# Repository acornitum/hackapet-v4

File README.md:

# hackapet pcb, v4

this is a wip!! it is not done yet

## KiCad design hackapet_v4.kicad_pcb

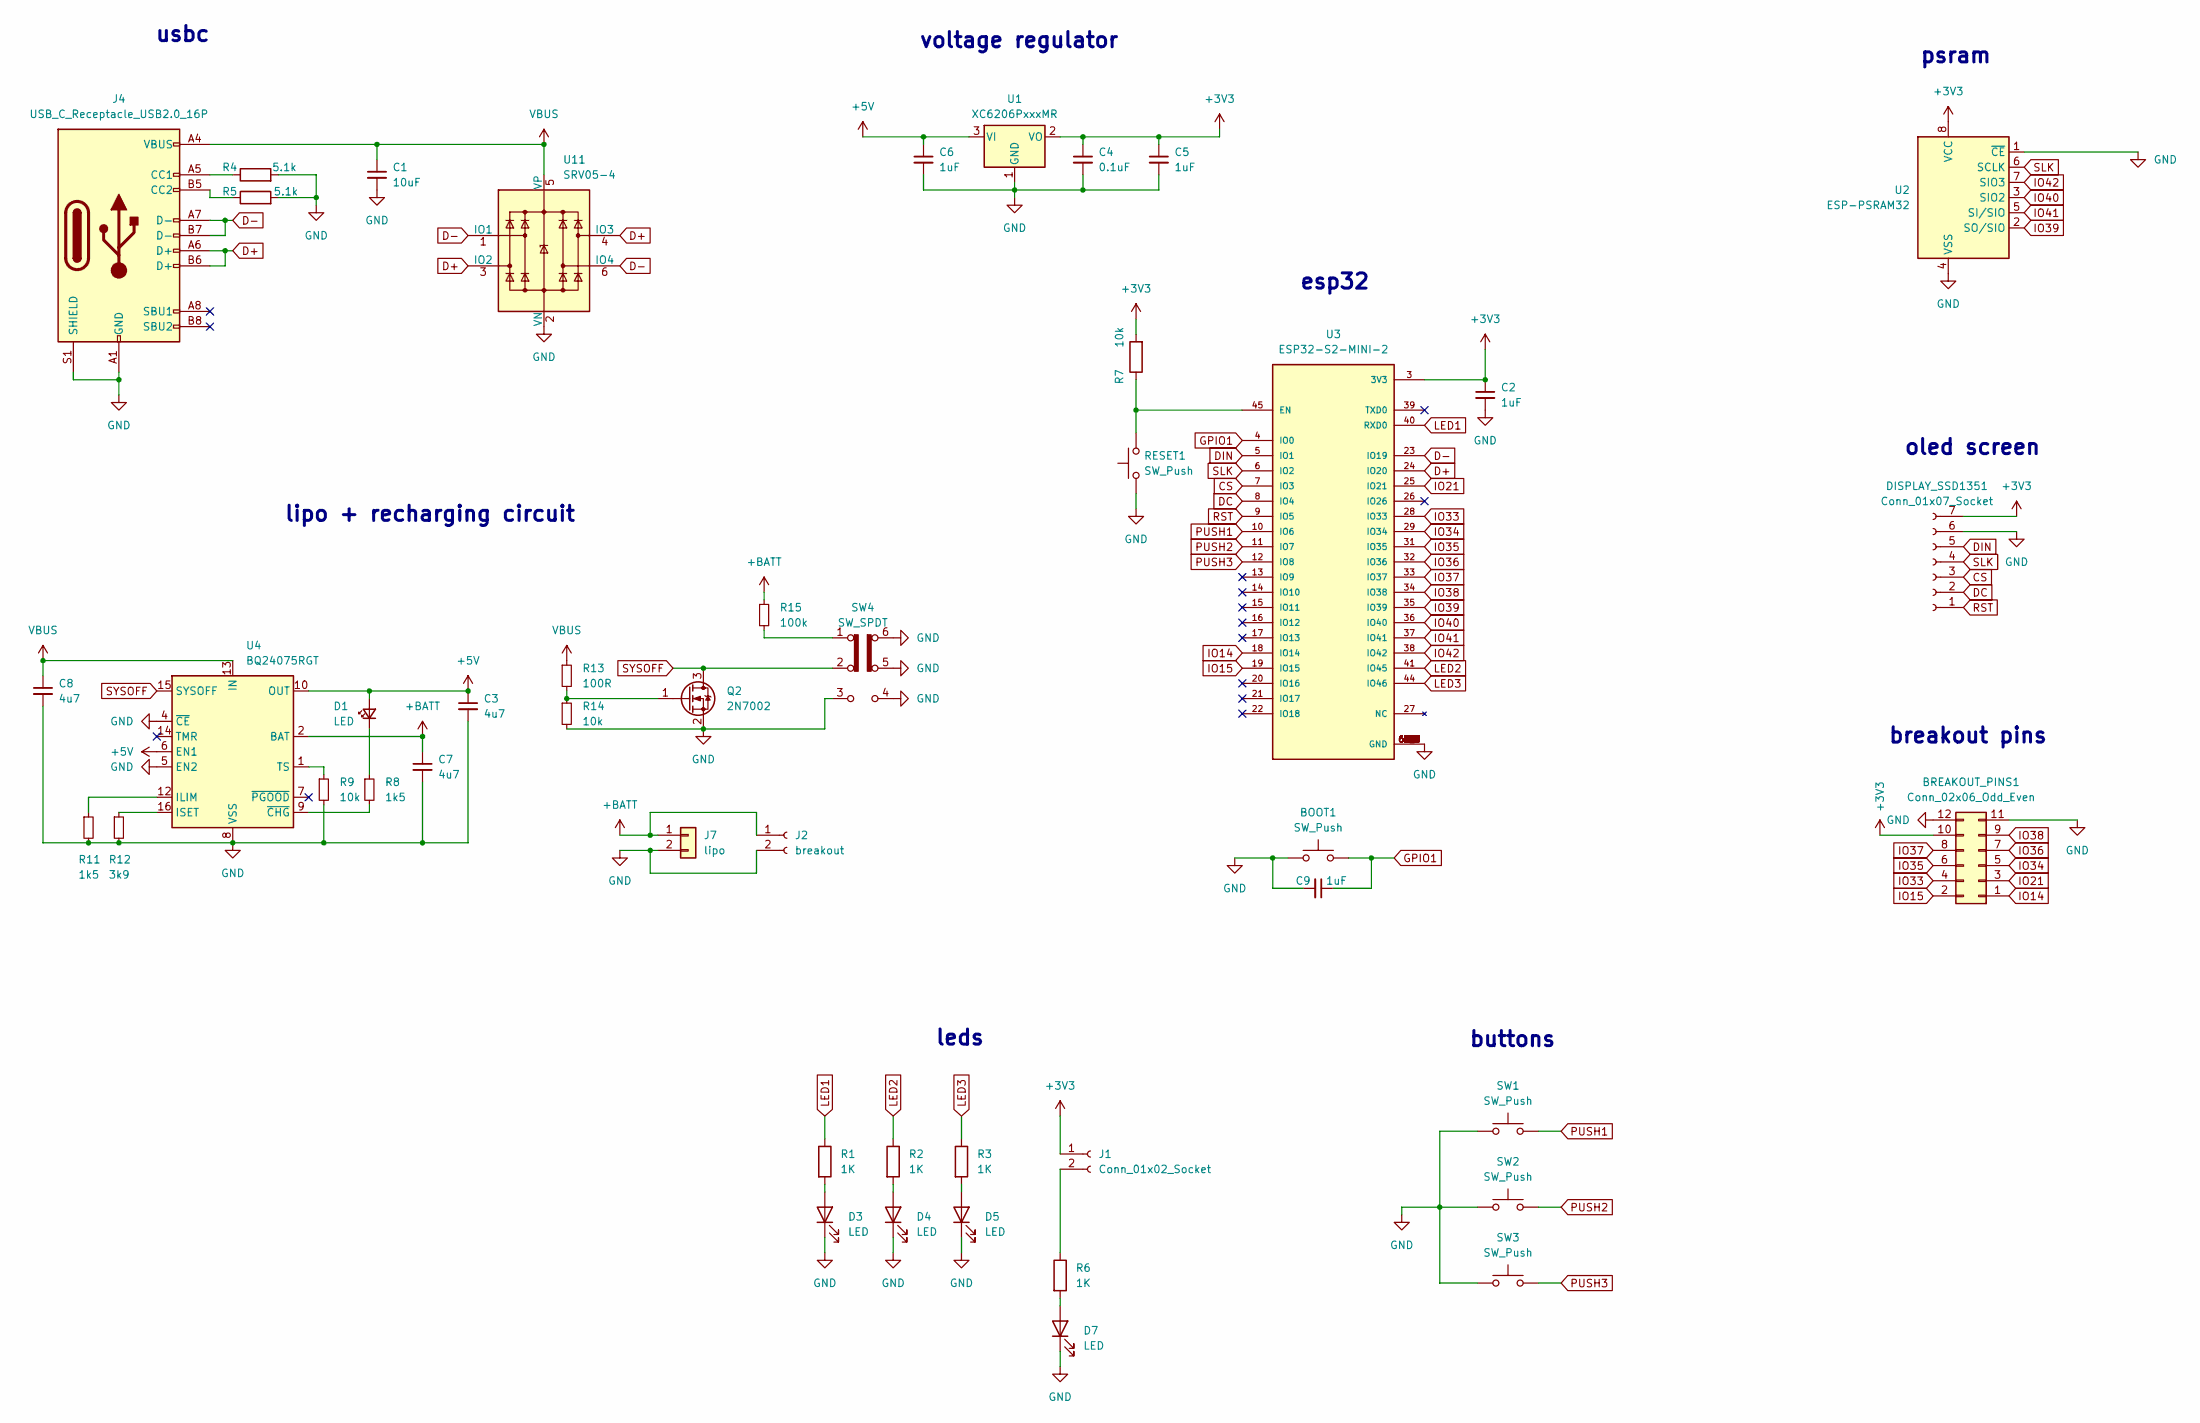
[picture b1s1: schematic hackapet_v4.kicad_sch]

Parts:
BOOT1: SW_Push; SW_Push_1P1T_XKB_TS-1187A; LCSC C381038
BREAKOUT_PINS1: Conn_02x06_Odd_Even; PinHeader_2x06_P2.54mm_Vertical
C1: 10uF; C_0805_2012Metric; LCSC C5189822
C2, C9: 1uF; C_0805_2012Metric; LCSC C215803
C3, C7, C8: 4u7; C_0805_2012Metric
C4: 0.1uF; C_0805_2012Metric; LCSC C28378
C5: 1uF; C_0805_2012Metric; LCSC C5189822
C6: 1uF; C_0805_2012Metric; LCSC C28378
D1, D3, D4, D5, D7: LED; LED_0805_2012Metric
DISPLAY_SSD1351: Conn_01x07_Socket; PinSocket_1x07_P2.54mm_Vertical; LCSC C22438073
J1: Conn_01x02_Socket; SolderJumper-2_P1.3mm_Open_Pad1.0x1.5mm
J2: breakout; PinHeader_1x02_P2.54mm_Vertical_SMD_Pin1Left
J4: USB_C_Receptacle_USB2.0_16P; USB_C_Receptacle_HCTL_HC-TYPE-C-16P-01A; LCSC C393939
J7: lipo; JST_PH_B2B-PH-K_1x02_P2.00mm_Vertical
Q2: 2N7002; SOT-23
R1, R2, R3, R6: 1K; R_0805_2012Metric; LCSC C17513
R4, R5: 5.1k; R_0805_2012Metric; LCSC C104375
R7, R9, R14: 10k; R_0805_2012Metric
R8, R11: 1k5; R_0805_2012Metric
R12: 3k9; R_0805_2012Metric
R13: 100R; R_0805_2012Metric
R15: 100k; R_0805_2012Metric
RESET1: SW_Push; SW_Push_1P1T_XKB_TS-1187A
SW1, SW2, SW3: SW_Push; SW_Push_1P1T_NO_6x6mm_H9.5mm; LCSC C381038
SW4: SW_SPDT; SW_DPDT_CK_JS202011JCQN; LCSC C221666
U1: XC6206PxxxMR; SOT-23-3
U2: ESP-PSRAM32; SOIC-8_3.9x4.9mm_P1.27mm
U3: ESP32-S2-MINI-2; XCVR_ESP32-S2-MINI-1; PARTREV 1.0; LCSC C3013906
U4: BQ24075RGT; VQFN-16-1EP_3x3mm_P0.5mm_EP1.6x1.6mm
U11: SRV05-4; SOT-23-6

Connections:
+3V3: BREAKOUT_PINS1.10, C2.1, C4.1, C5.1, DISPLAY_SSD1351.7, J1.1, R7.2, U1.2 (VO), U2.8 (VCC), U3.3 (3V3)
+5V: C3.1, C6.1, D1.2 (A), U1.3 (VI), U4.6 (EN1), U4.10 (OUT), U4.11 (OUT)
+BATT: C7.1, J2.1, J7.1, R15.1, U4.2 (BAT), U4.3 (BAT)
CS: DISPLAY_SSD1351.3, U3.7 (IO3)
D+: J4.A6 (D+), J4.B6 (D+), U3.24 (IO20), U11.3 (IO2), U11.4 (IO3)
D-: J4.A7 (D-), J4.B7 (D-), U3.23 (IO19), U11.1 (IO1), U11.6 (IO4)
DC: DISPLAY_SSD1351.2, U3.8 (IO4)
DIN: DISPLAY_SSD1351.5, U3.5 (IO1)
GND: BOOT1.1, BREAKOUT_PINS1.11, BREAKOUT_PINS1.12, C1.2, C2.2, C3.2, C4.2, C5.2, C6.2, C7.2, C8.2, C9.2, D3.1 (K), D4.1 (K), D5.1 (K), D7.1 (K), DISPLAY_SSD1351.6, J2.2, J4.A1 (GND), J4.A12 (GND), J4.B1 (GND), J4.B12 (GND), J4.S1 (SHIELD), J7.2, Q2.2 (S), R4.2, R5.2, R9.2, R11.2, R12.2, R14.2, RESET1.1, SW1.1, SW2.1, SW3.1, SW4.3 (C), SW4.4 (A), SW4.5 (B), SW4.6 (C), U1.1 (GND), U2.1 (~CE), U2.4 (VSS), U3.1 (GND), U3.2 (GND), U3.30 (GND), U3.42 (GND), U3.43 (GND), U3.46 (GND), U3.47 (GND), U3.48 (GND), U3.49 (GND), U3.50 (GND), U3.51 (GND), U3.52 (GND), U3.53 (GND), U3.54 (GND), U3.55 (GND), U3.56 (GND), U3.57 (GND), U3.58 (GND), U3.59 (GND), U3.60 (GND), U3.61 (GND), U3.61_1 (GND), U3.61_2 (GND), U3.61_3 (GND), U3.61_4 (GND), U3.61_5 (GND), U3.61_6 (GND), U3.61_7 (GND), U3.61_8 (GND), U3.62 (GND), U3.63 (GND), U3.64 (GND), U3.65 (GND), U4.4 (~CE), U4.5 (EN2), U4.8 (VSS), U4.17 (VSS), U11.2 (VN)
GPIO1: BOOT1.2, C9.1, U3.4 (IO0)
IO14: BREAKOUT_PINS1.1, U3.18 (IO14)
IO15: BREAKOUT_PINS1.2, U3.19 (IO15)
IO21: BREAKOUT_PINS1.3, U3.25 (IO21)
IO33: BREAKOUT_PINS1.4, U3.28 (IO33)
IO34: BREAKOUT_PINS1.5, U3.29 (IO34)
IO35: BREAKOUT_PINS1.6, U3.31 (IO35)
IO36: BREAKOUT_PINS1.7, U3.32 (IO36)
IO37: BREAKOUT_PINS1.8, U3.33 (IO37)
IO38: BREAKOUT_PINS1.9, U3.34 (IO38)
IO39: U2.2 (SO/SIO), U3.35 (IO39)
IO40: U2.3 (SIO2), U3.36 (IO40)
IO41: U2.5 (SI/SIO), U3.37 (IO41)
IO42: U2.7 (SIO3), U3.38 (IO42)
LED1: R1.1, U3.40 (RXD0)
LED2: R2.1, U3.41 (IO45)
LED3: R3.1, U3.44 (IO46)
unnamed: D1.1 (K), R8.1
unnamed: D3.2 (A), R1.2
unnamed: D4.2 (A), R2.2
unnamed: D5.2 (A), R3.2
unnamed: D7.2 (A), R6.2
unnamed: J1.2, R6.1
unnamed: J4.A5 (CC1), R4.1
unnamed: J4.B5 (CC2), R5.1
unnamed: Q2.1 (G), R13.2, R14.1
unnamed: R15.2, SW4.1 (A)
unnamed: R7.1, RESET1.2, U3.45 (EN)
unnamed: R11.1, U4.12 (ILIM)
unnamed: R12.1, U4.16 (ISET)
unnamed: R9.1, U4.1 (TS)
unnamed: R8.2, U4.9 (~CHG)
PUSH1: SW1.2, U3.10 (IO6)
PUSH2: SW2.2, U3.11 (IO7)
PUSH3: SW3.2, U3.12 (IO8)
RST: DISPLAY_SSD1351.1, U3.9 (IO5)
SLK: DISPLAY_SSD1351.4, U2.6 (SCLK), U3.6 (IO2)
SYSOFF: Q2.3 (D), SW4.2 (B), U4.15 (SYSOFF)
VBUS: C1.1, C8.1, J4.A4 (VBUS), J4.A9 (VBUS), J4.B4 (VBUS), J4.B9 (VBUS), R13.1, U4.13 (IN), U11.5 (VP)

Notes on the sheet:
leds
lipo + recharging circuit
buttons
usbc
esp32
psram
voltage regulator
oled screen
breakout pins

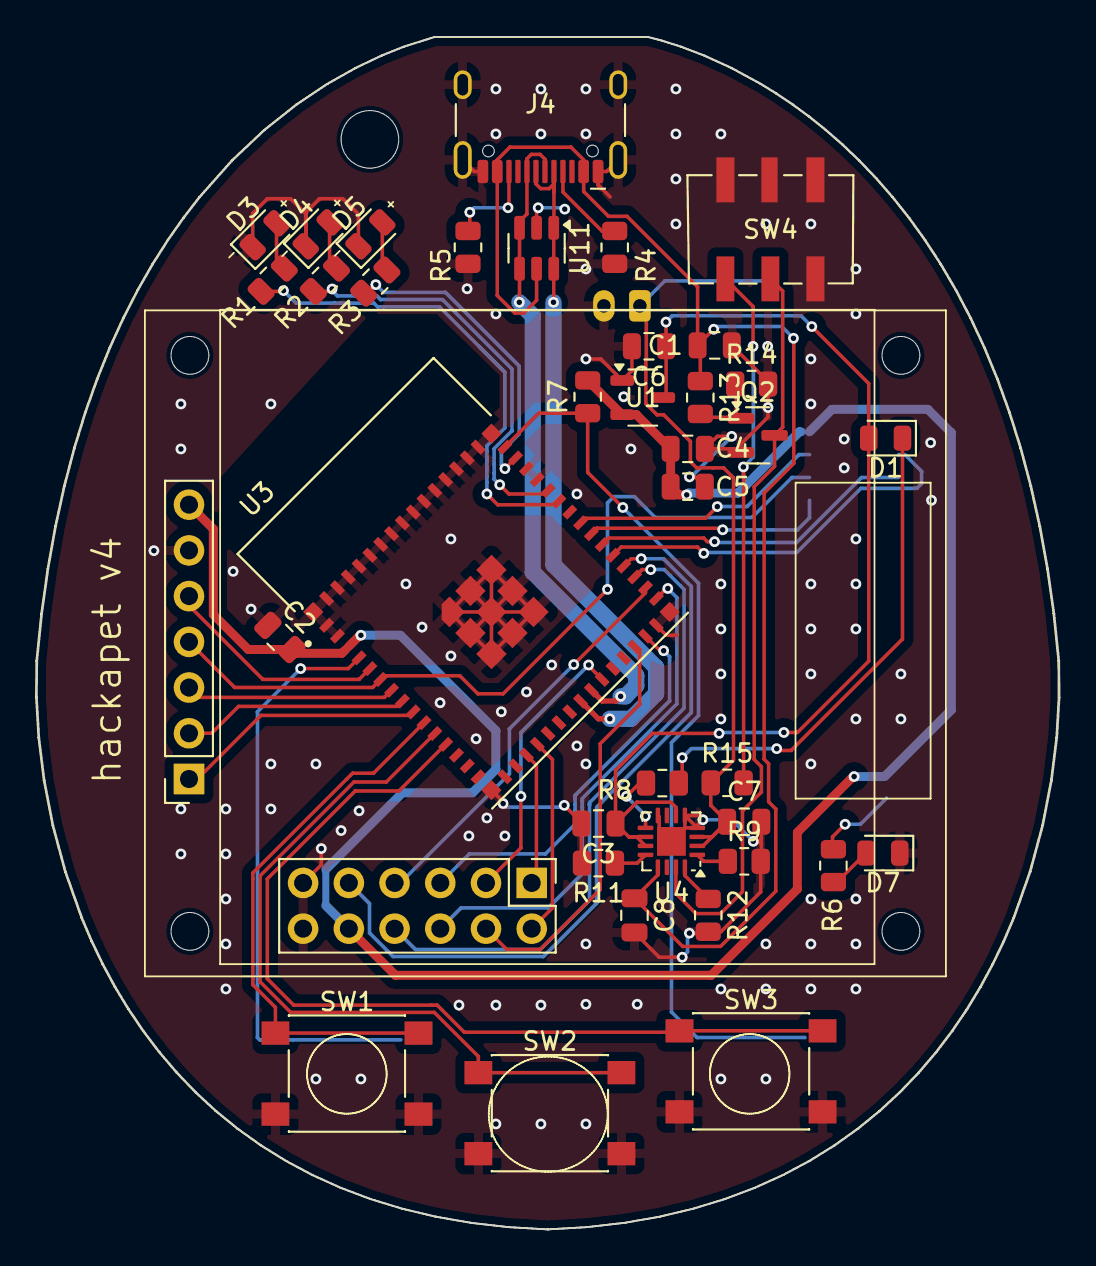
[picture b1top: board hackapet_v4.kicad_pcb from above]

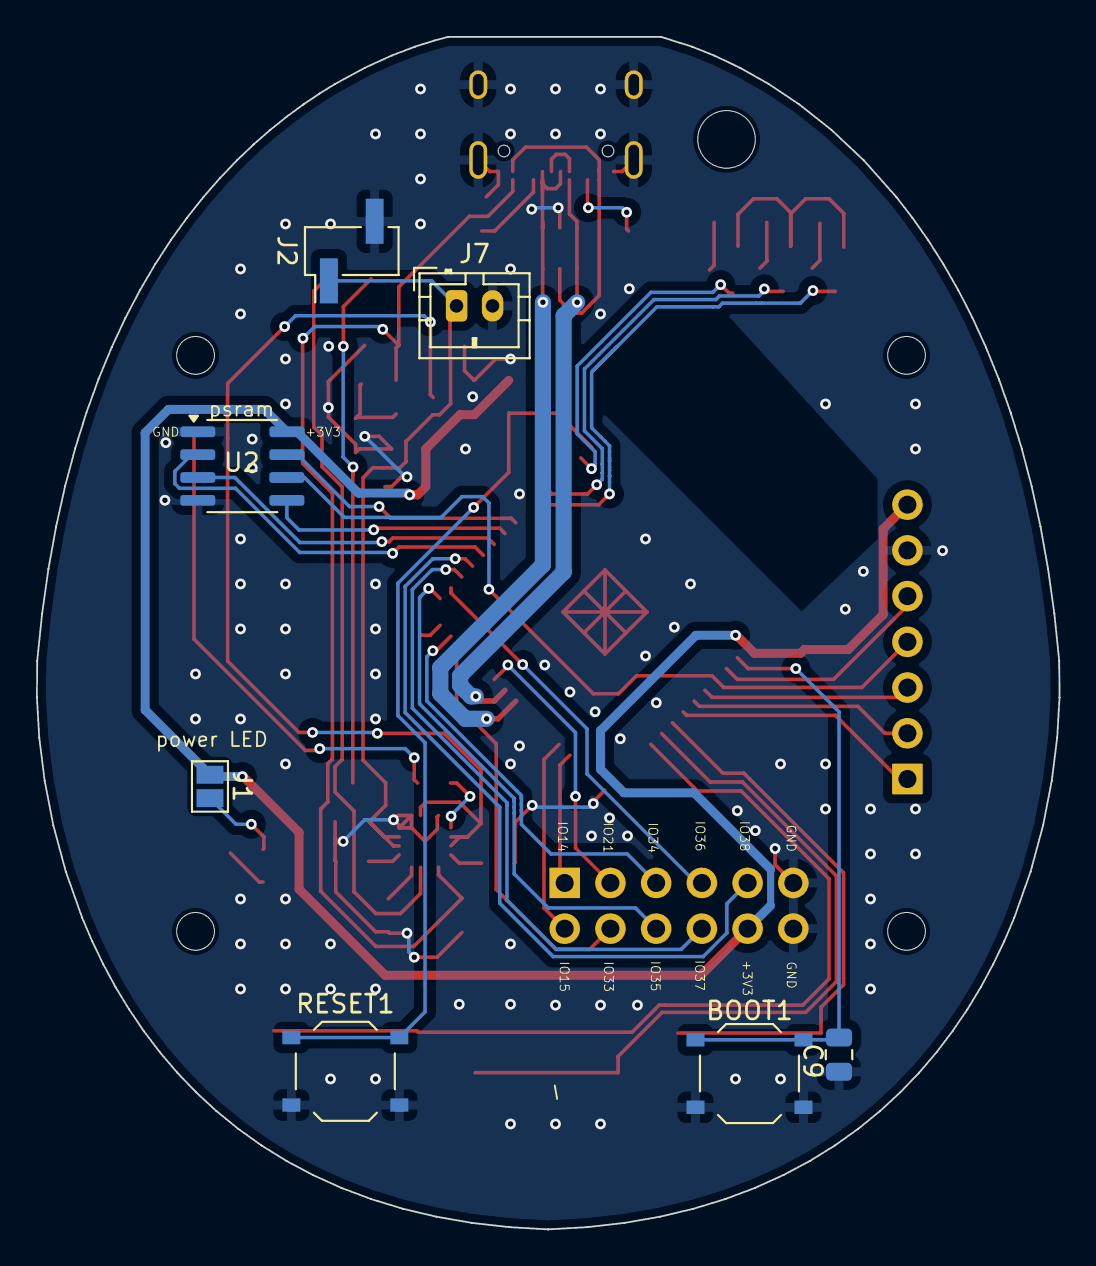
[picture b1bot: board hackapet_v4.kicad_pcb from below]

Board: 2 copper layers, 56.8 x 66.2 mm, 46 parts (7 on the bottom side), 48 nets.

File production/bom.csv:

Designator,Footprint,Quantity,Value,LCSC Part #
BOOT1,SW_Push_1P1T_XKB_TS-1187A,1,SW_Push,C381038
BREAKOUT_PINS1,PinHeader_2x06_P2.54mm_Vertical,1,Conn_02x06_Odd_Even,
C1,0805,1,10uF,C5189822
"C2, C9",0805,2,1uF,C215803
"C3, C7, C8",0805,3,4u7,
C4,0805,1,0.1uF,C28378
C5,0805,1,1uF,C5189822
C6,0805,1,1uF,C28378
"D1, D7",0805,2,LED,
D3,0805,1,LED,C192672
D4,0805,1,LED,C192319
D5,0805,1,LED,C192320
DISPLAY_SSD1351,PinSocket_1x07_P2.54mm_Vertical,1,Conn_01x07_Socket,C22438073
J1,SolderJumper-2_P1.3mm_Open_Pad1.0x1.5mm,1,Conn_01x02_Socket,
J4,USB_C_Receptacle_HCTL_HC-TYPE-C-16P-01A,1,USB_C_Receptacle_USB2.0_16P,C393939
J7,JST_PH_B2B-PH-K_1x02_P2.00mm_Vertical,1,lipo,
Q2,SOT-23,1,2N7002,
"R1, R2, R3, R6",0805,4,1K,C17513
"R11, R8",0805,2,1k5,
R12,0805,1,3k9,
R13,0805,1,100R,
"R14, R7, R9",0805,3,10k,
R15,0805,1,100k,
"R4, R5",0805,2,5.1k,C104375
RESET1,SW_Push_1P1T_XKB_TS-1187A,1,SW_Push,
"SW1, SW2, SW3",SW_Push_1P1T_NO_6x6mm_H9.5mm,3,SW_Push,C381038
SW4,SW_DPDT_CK_JS202011JCQN,1,SW_SPDT,C221666
U1,SOT-23-3,1,XC6206PxxxMR,
U11,SOT-23-6,1,SRV05-4,
U2,SOIC-8_3.9x4.9mm_P1.27mm,1,ESP-PSRAM32,
U3,XCVR_ESP32-S2-MINI-1,1,ESP32-S2-MINI-2,C3013906
U4,VQFN-16-1EP_3x3mm_P0.5mm_EP1.6x1.6mm,1,BQ24075RGT,

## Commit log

2026-01-08 add readme
2026-01-18 routed!
2026-01-18 add stitching vias
2026-01-18 add keepout, thicken 3v3 to .5
2026-01-26 final updates!
